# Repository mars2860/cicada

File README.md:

### About

The Cicada Project is the flight controller based on ESP8266 Wifi module. You can make it yourself to come in the world of drone developers. Cicada doesn't have a hardware pult with sticks. To control a drone there is desktop application developed on Java and mobile application for Android v7 and higher. You can connect a gamepad to your smartphone or desktop to control a drone. The flight controller can work in WiFi normal mode as WiFi station or WiFi Access Point. Also It can work in WiFi Broadcast mode (WiFi monitor mode). To work in broadcast mode you have to connect the special wifi broadcast serial modem to your smartphone or desktop. The serial modem is easy. You can do it yourself easy. Just ESP-07 module + UART-USB bridge. Flash in ESP-07 the modem firmware which is placed in the folder /firmware/WifiBroadcastModemFw.

### Features

|     |     |     |     |
| --- | --- | --- | --- |
|     | **Min** | **Typ** | **Max** |
| **1\. Supply voltage** | 3,4V |     | 5V  |
| **2\. Update frequency** |     | 100 Hz |     |
| **3\. Control from notebook or smartphone through WiFi net.** |     | 2.4 GHz |     |
| **4\. Instant telemetry through WiFi net.** Charts of all parameters. BlackBox is stored on host. Telemetry packets is sent every 10ms. |     |     |     |
| **5\. Control devices:**<br><br>* Gamepad (supported by desktop and mobile applications)<br>* Keyboard (supported by desktop application only)<br>* Virtual keyboard (supported by desktop application only)<br>* Virtual gamepad (supported by mobile application only) |     |     |     |
| **6\. Control range** |     |     | 100 meters |
| **7\. Stabilization modes:**<br><br>* Stabilization of body angular rates<br>* Stabilization of yaw,pitch,roll angles<br>* Stabilization of vertical velocity (only if barometer or lidar are available in the system)<br>* Stabilization of horizontal velocity (only if optical flow sensor or GPS are available in the system) |     |     |     |
| **8\. Supported sensors and devices:**<br><br>* MPU9250 - imu chip<br>* MPU6500 - imu chip<br>* MPU6050 - imu chip<br>* QMC5883L - magnetometer<br>* BMP280 - barometer<br>* VL53L1X - lidar<br>* TFmini Plus (in I2C mode) - lidar<br>* HCSR04 (in I2C mode) - sonar<br>* BN180 and other GPS modules with UBX protocol<br>* Analog 0-3V sensor of battery current<br>* Servo 500-2400us to control camera pitch angle<br>* Camera Runcam Split4 (only supported start/stop video commands) |     |     |     |
| **9\. Electronic speed controllers:**<br><br>* DSHOT-300 to control BLDC motors<br>* All listed below PWM-modesе to direct control coreless dc motors<br>* PWM 2.5 kHz, resolution 2000<br>* PWM 5 kHz, resolution 1000<br>* PWM 10 kHz, resolution 500<br>* PWM 20 kHz, resolution 250<br>* PWM 40 kHz, resolution 125<br>* PWM 50 kHz, resolution 100 |     |     |     |
| **10\. Dimensions**<br><br>* cicada-main-v4<br>* cicada-micro-v2 |     | 58,67mm х 41,65mm  <br>26,67mm x 30,98mm |     |
| **11\. Installation dimensions**<br><br>* cicada-main-v4<br>* cicada-micro-v2 |     | 48,51mm х 31,49mm  <br>21,84mm x 26,16mm |     |
| **12\. Weight**<br><br>* cicada-main-v4 with cicada-gy91-v3<br>* cicada-micro-v2 |     | 16g  <br>6g |     |
	
### Drones

Examples of drones you can find in drones folder of this project.

### Firmware

The firmware is based on PDL. Portable Drone Logic (PDL) is the lightweight pure C library implements a common drone logic. The goal of PDL is to be easy to use and easy to port to your hardware platform. PDL supports only quadcopters at this time.

It provides for you
- data model
- application template
- task scheduler
- chain of PIDs
- parser for binary digital commands

PDL is a part of this project. But you can use it to create firmware for your own hardware platform. Documentation is available in /firmware/CicadaFw/libraries/pdl

To build firmware you need
- Install Sloeber IDE https://github.com/Sloeber/arduino-eclipse-plugin/releases/
- Run Sloeber IDE. Go to Arduino->Preferences->Platforms and Boards. Download latest version of ESP8266 platform
- Install I2C driver https://github.com/enjoyneering/ESP8266-I2C-Driver
- Create ssid_config.h file with your wifi-net settings. For example

Firmware supports update by the air. It is based on ESP8266HTTPUpdateServer.

### Chain of PIDs

### Design tools

- Sloeber IDE
- FreeCAD
- KiCAD

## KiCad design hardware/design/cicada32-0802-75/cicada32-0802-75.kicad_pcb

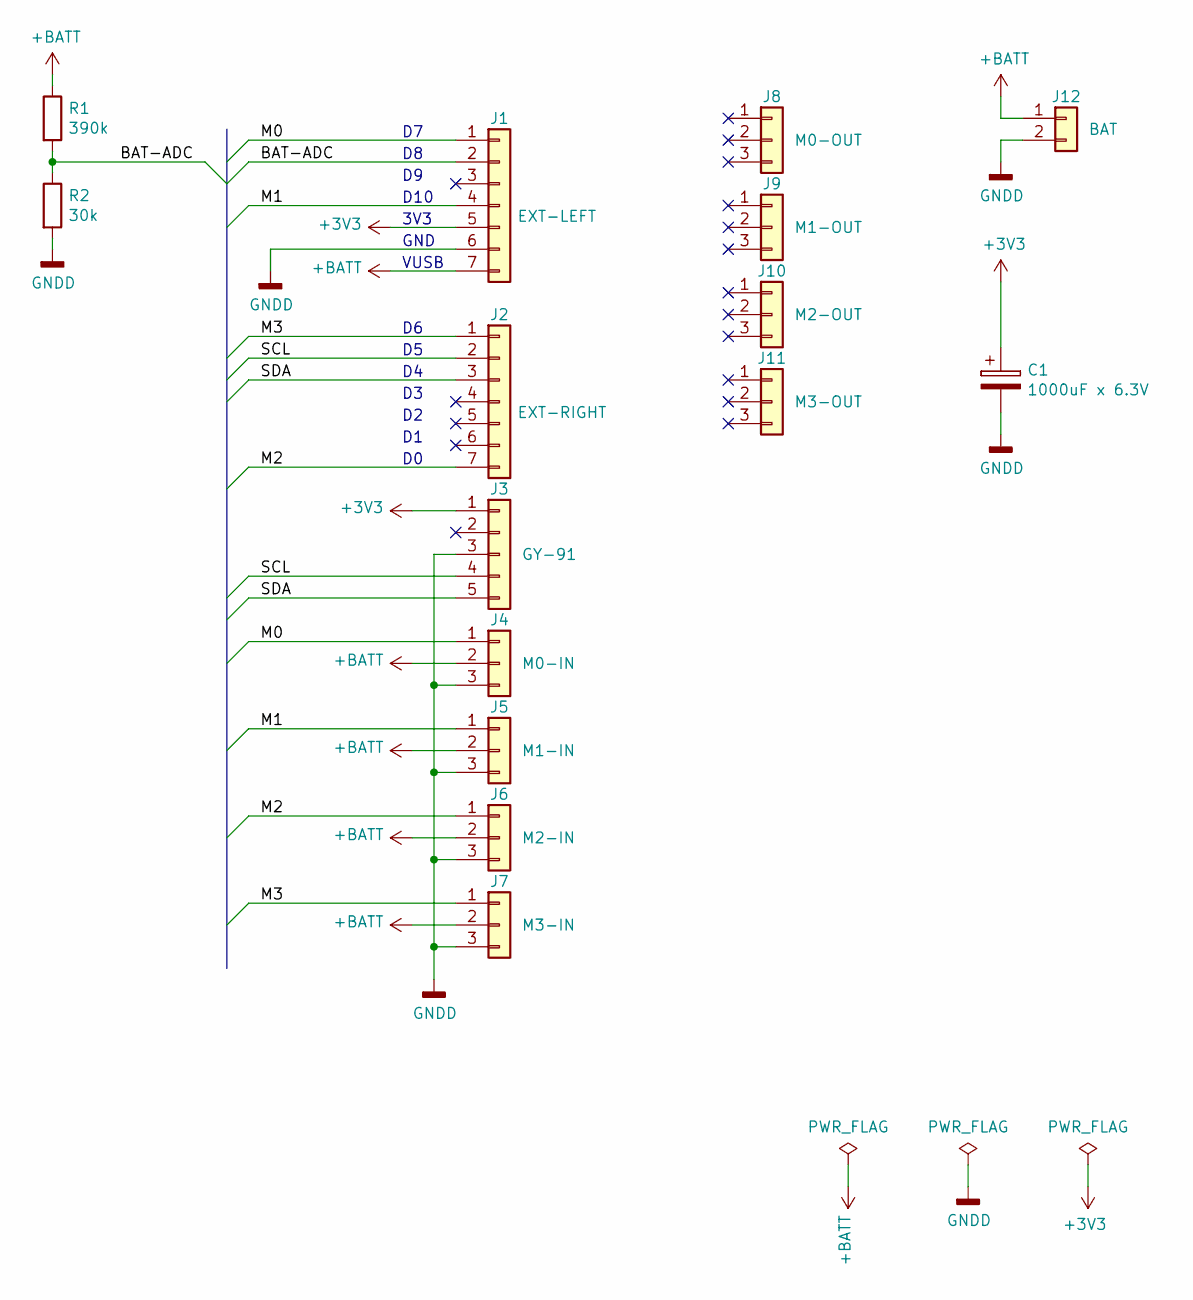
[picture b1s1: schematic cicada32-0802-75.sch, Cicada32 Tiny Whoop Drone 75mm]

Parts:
C1: 1000uF x 6.3V; CP_Radial_D8.0mm_P3.50mm
J1: EXT-LEFT; PinSocket_1x07_P2.54mm_Vertical
J2: EXT-RIGHT; PinSocket_1x07_P2.54mm_Vertical
J3: GY-91; PinHeader_1x05_P2.54mm_Vertical
J4: M0-IN; PinHeader_1x03_P2.54mm_Vertical
J5: M1-IN; PinHeader_1x03_P2.54mm_Vertical
J6: M2-IN; PinHeader_1x03_P2.54mm_Vertical
J7: M3-IN; PinHeader_1x03_P2.54mm_Vertical
J8: M0-OUT; PinHeader_1x03_P2.54mm_Vertical
J9: M1-OUT; PinHeader_1x03_P2.54mm_Vertical
J10: M2-OUT; PinHeader_1x03_P2.54mm_Vertical
J11: M3-OUT; PinHeader_1x03_P2.54mm_Vertical
J12: BAT; SolderWirePad_1x02_P3.81mm_Drill1.2mm
R1: 390k; R_0805_2012Metric_Pad1.15x1.40mm_HandSolder
R2: 30k; R_0805_2012Metric_Pad1.15x1.40mm_HandSolder

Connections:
+3V3: C1.1, J1.5, J3.1
+BATT: J1.7, J4.2, J5.2, J6.2, J7.2, J12.1, R1.1
/BAT-ADC: J1.2, R1.2, R2.1
/M0: J1.1, J4.1
/M1: J1.4, J5.1
/M2: J2.7, J6.1
/M3: J2.1, J7.1
/SCL: J2.2, J3.4
/SDA: J2.3, J3.5
GNDD: C1.2, J1.6, J3.3, J4.3, J5.3, J6.3, J7.3, J12.2, R2.2

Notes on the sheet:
D10
3V3
GND
VUSB

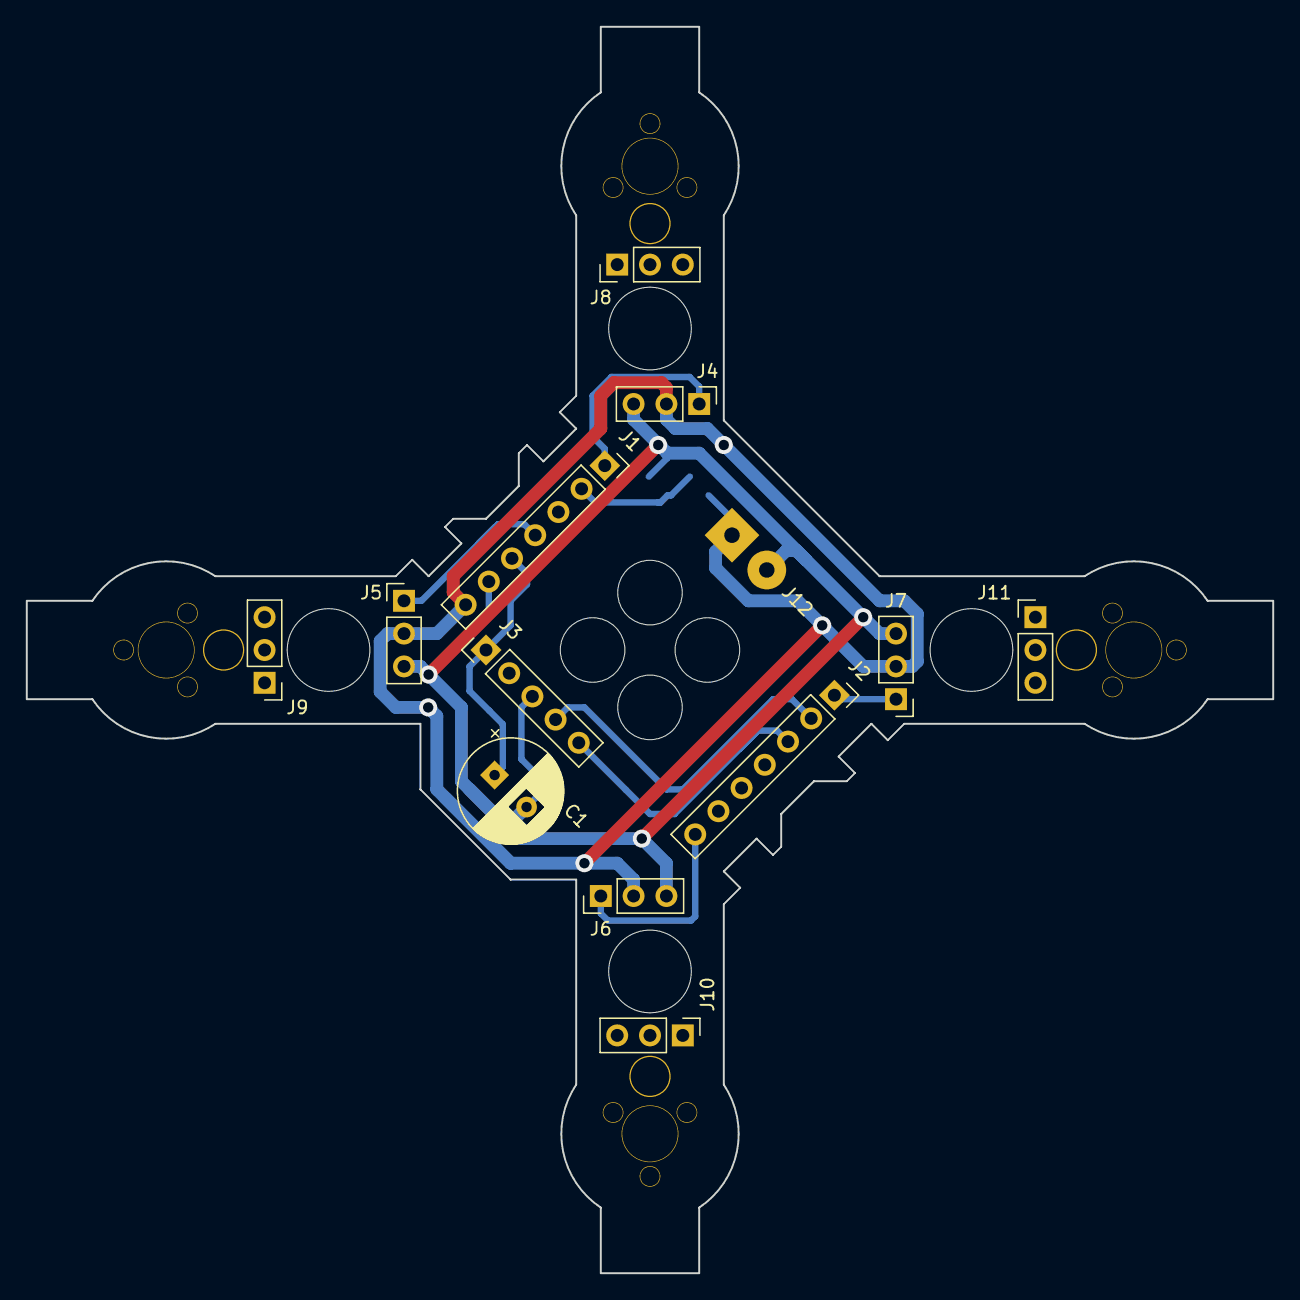
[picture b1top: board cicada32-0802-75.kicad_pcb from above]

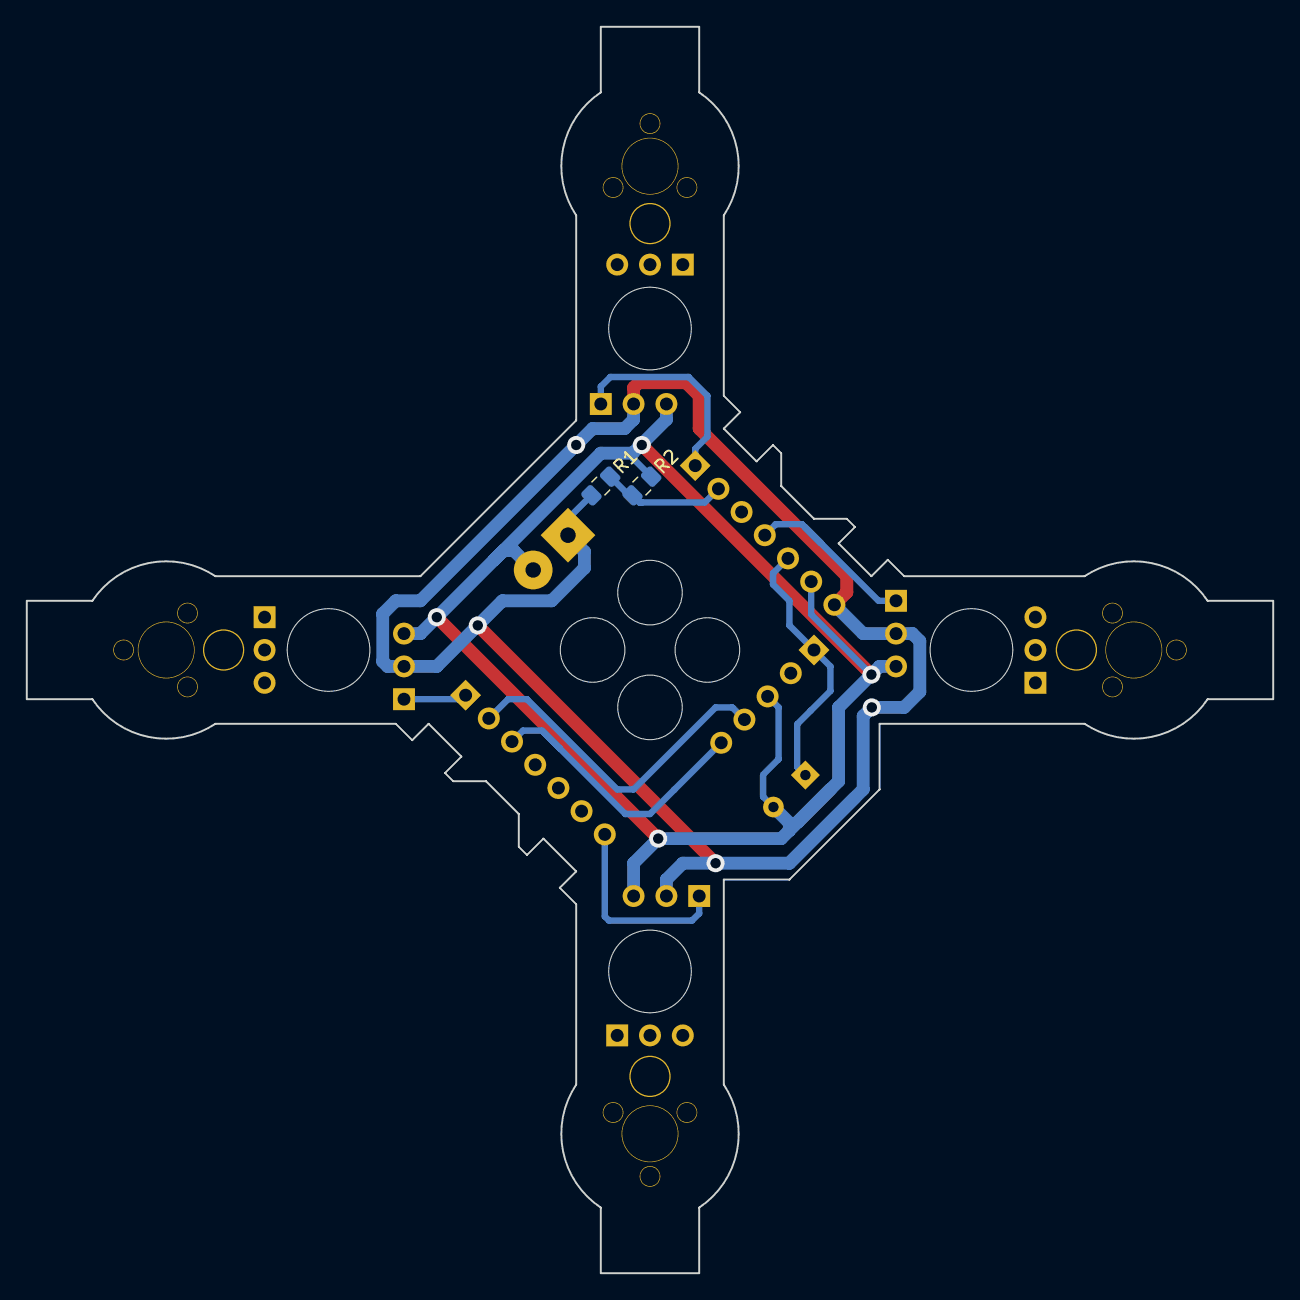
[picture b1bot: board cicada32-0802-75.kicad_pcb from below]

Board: 2 copper layers, 96.5 x 96.5 mm, 15 parts (2 on the bottom side), 10 nets.

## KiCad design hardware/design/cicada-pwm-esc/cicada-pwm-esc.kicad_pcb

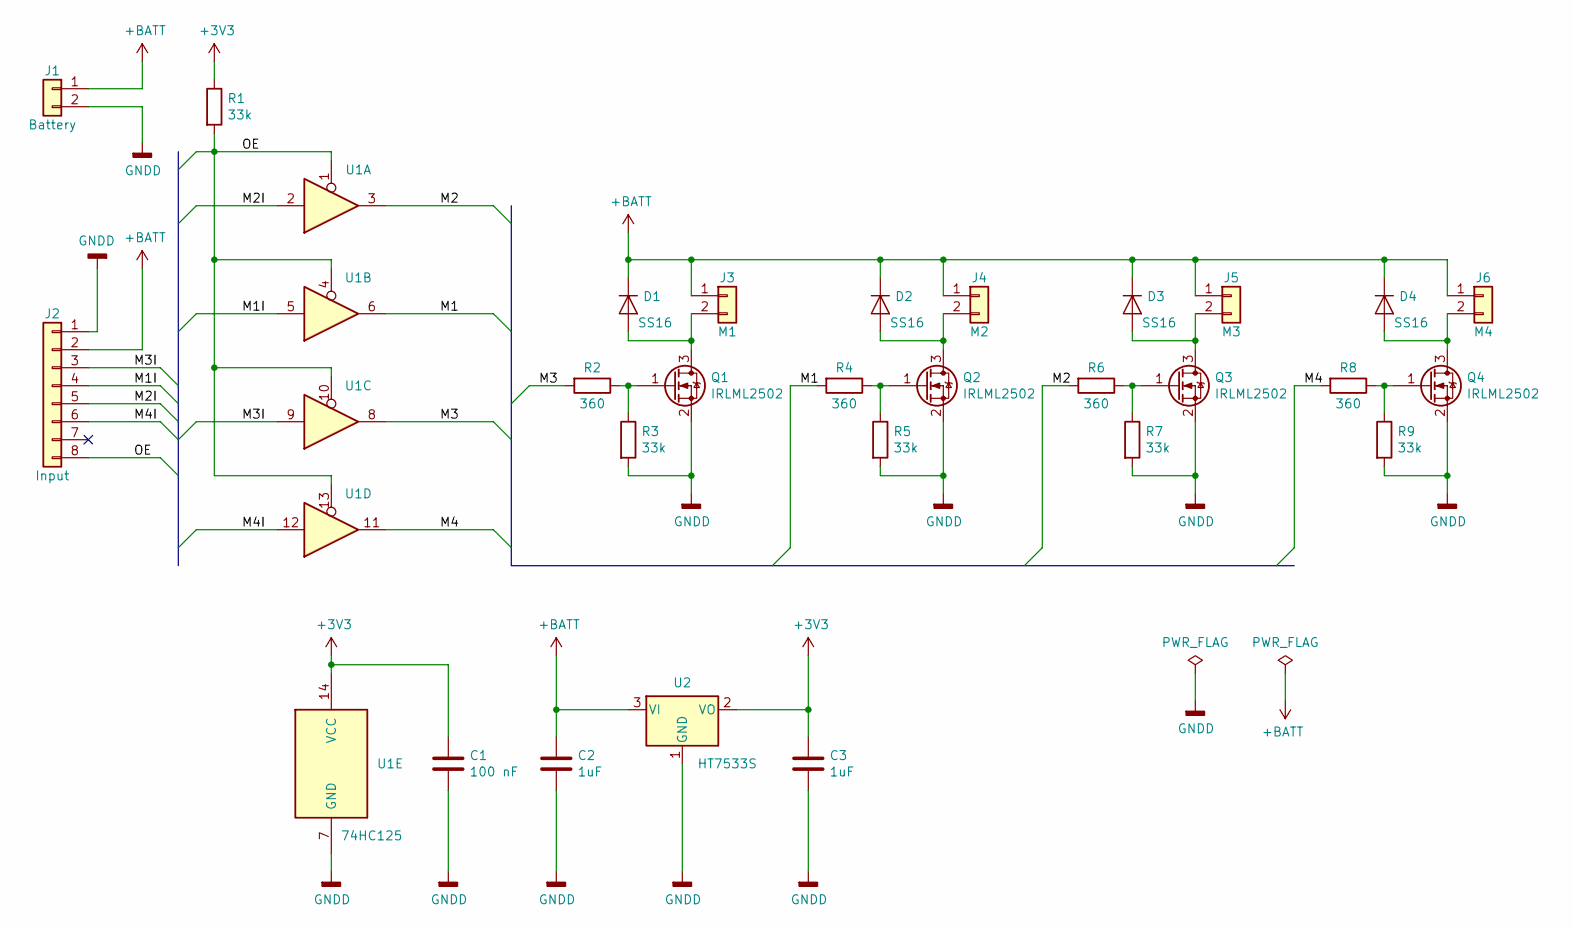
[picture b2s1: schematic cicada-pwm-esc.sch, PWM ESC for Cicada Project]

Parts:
C1: 100 nF; C_0805_2012Metric
C2, C3: 1uF; C_0805_2012Metric
D1, D2, D3, D4: SS16; D_SMA
J1: Battery; SolderWirePad_1x02_P5.08mm_Drill1.5mm
J2: Input; Molex_PicoBlade_53047-1610_1x08_P1.25mm_Vertical
J3: M1; Molex_PicoBlade_53047-0410_1x02_P1.25mm_Vertical
J4: M2; Molex_PicoBlade_53047-0410_1x02_P1.25mm_Vertical
J5: M3; Molex_PicoBlade_53047-0410_1x02_P1.25mm_Vertical
J6: M4; Molex_PicoBlade_53047-0410_1x02_P1.25mm_Vertical
Q1, Q2, Q3, Q4: IRLML2502; SOT-23
R1, R3, R5, R7, R9: 33k; R_0805_2012Metric
R2, R4, R6, R8: 360; R_0805_2012Metric
U1: 74HC125; SOIC-14_3.9x8.7mm_P1.27mm
U2: HT7533S; SOT-23

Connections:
+3V3: C1.1, C3.1, R1.1, U1.14 (VCC), U2.2 (VO)
+BATT: C2.1, D1.1 (K), D2.1 (K), D3.1 (K), D4.1 (K), J1.1, J2.2, J3.1, J4.1, J5.1, J6.1, U2.3 (VI)
/M1: R4.2, U1.6
/M1I: J2.4, U1.5
/M2: R6.2, U1.3
/M2I: J2.5, U1.2
/M3: R2.2, U1.8
/M3I: J2.3, U1.9
/M4: R8.2, U1.11
/M4I: J2.6, U1.12
/OE: J2.8, R1.2, U1.1, U1.4, U1.10, U1.13
GNDD: C1.2, C2.2, C3.2, J1.2, J2.1, Q1.2 (S), Q2.2 (S), Q3.2 (S), Q4.2 (S), R3.2, R5.2, R7.2, R9.2, U1.7 (GND), U2.1 (GND)
unnamed: D1.2 (A), J3.2, Q1.3 (D)
unnamed: D2.2 (A), J4.2, Q2.3 (D)
unnamed: D3.2 (A), J5.2, Q3.3 (D)
unnamed: D4.2 (A), J6.2, Q4.3 (D)
unnamed: Q1.1 (G), R2.1, R3.1
unnamed: Q2.1 (G), R4.1, R5.1
unnamed: Q3.1 (G), R6.1, R7.1
unnamed: Q4.1 (G), R8.1, R9.1

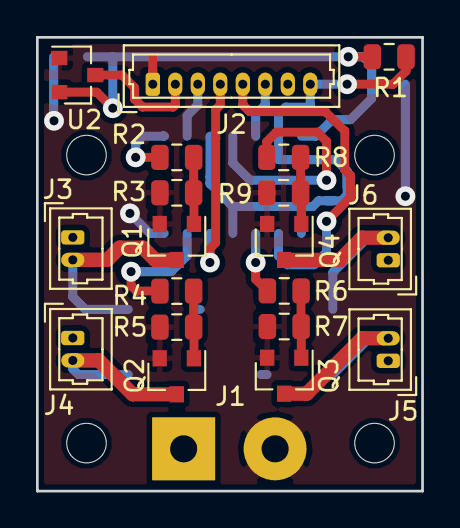
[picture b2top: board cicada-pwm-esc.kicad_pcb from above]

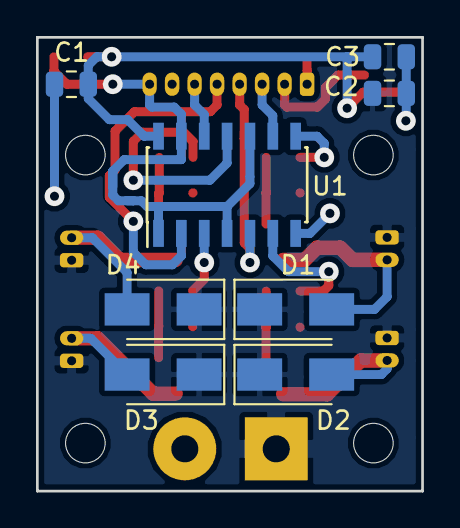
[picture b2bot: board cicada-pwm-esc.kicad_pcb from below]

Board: 2 copper layers, 21.4 x 25.2 mm, 28 parts (8 on the bottom side), 20 nets.

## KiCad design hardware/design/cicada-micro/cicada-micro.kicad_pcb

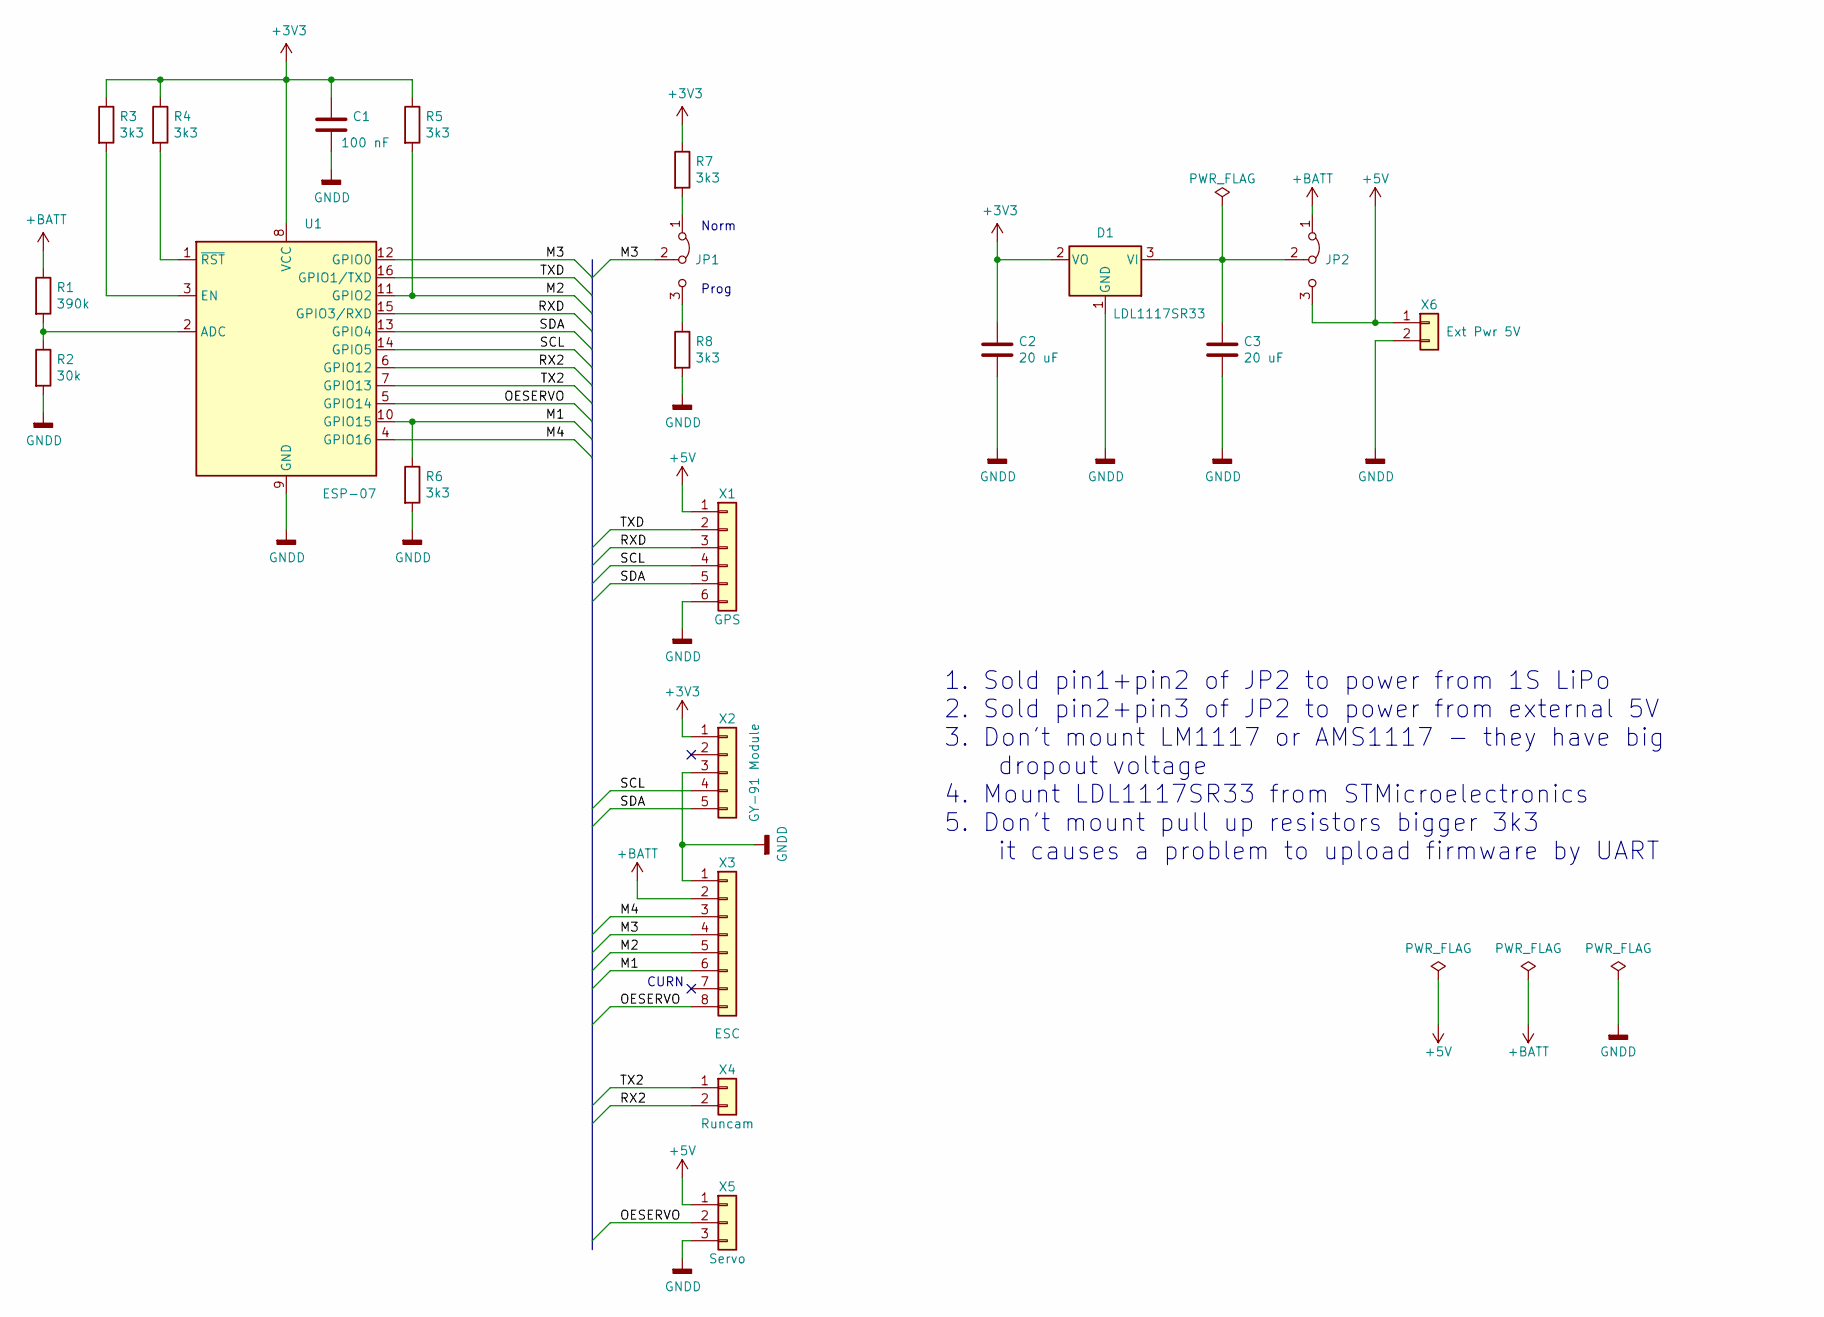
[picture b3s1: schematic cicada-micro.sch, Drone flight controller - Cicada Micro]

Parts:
C1: 100 nF; C_0805_2012Metric
C2, C3: 20 uF; C_1206_3216Metric
D1: LDL1117SR33; SOT-223-3_TabPin2
JP1, JP2: Jumper_3_Bridged12; SolderJumper-3_P1.3mm_Open_Pad1.0x1.5mm
R1: 390k; R_0805_2012Metric
R2: 30k; R_0805_2012Metric
R3, R4, R5, R6, R7, R8: 3k3; R_0805_2012Metric
U1: ESP-07; ESP-07-ThroughMount
X1: GPS; Molex_PicoBlade_53047-1210_1x06_P1.25mm_Vertical
X2: GY-91 Module; PinHeader_1x05_P2.54mm_Vertical
X3: ESC; Molex_PicoBlade_53047-1610_1x08_P1.25mm_Vertical
X4: Runcam; Molex_PicoBlade_53047-0410_1x02_P1.25mm_Vertical
X5: Servo; Molex_PicoBlade_53047-0610_1x03_P1.25mm_Vertical
X6: Ext Pwr 5V; Molex_PicoBlade_53047-0410_1x02_P1.25mm_Vertical

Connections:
+3V3: C1.1, C2.1, D1.2 (VO), R3.1, R4.1, R5.1, R7.1, U1.8 (VCC), X2.1
+5V: JP2.3 (B), X1.1, X5.1, X6.1; also elsewhere on the board
+BATT: JP2.1 (A), R1.1, X3.2; also elsewhere on the board
/M1: R6.1, U1.10 (GPIO15), X3.6
/M2: R5.2, U1.11 (GPIO2), X3.5
/M3: JP1.2 (C), U1.12 (GPIO0), X3.4
/M4: U1.4 (GPIO16), X3.3
/OESERVO: U1.5 (GPIO14), X3.8, X5.2
/RX2: U1.6 (GPIO12), X4.2
/RXD: U1.15 (GPIO3/RXD), X1.3
/SCL: U1.14 (GPIO5), X1.4, X2.4
/SDA: U1.13 (GPIO4), X1.5, X2.5
/TX2: U1.7 (GPIO13), X4.1
/TXD: U1.16 (GPIO1/TXD), X1.2
GNDD: C1.2, C2.2, C3.2, D1.1 (GND), R2.2, R6.2, R8.2, U1.9 (GND), X1.6, X2.3, X3.1, X5.3, X6.2
unnamed 15: C3.1, D1.3 (VI), JP2.2 (C); also elsewhere on the board
unnamed: JP1.1 (A), R7.2
unnamed: JP1.3 (B), R8.1
unnamed: R1.2, R2.1, U1.2 (ADC)
unnamed: R3.2, U1.3 (EN)
unnamed: R4.2, U1.1 (~RST)

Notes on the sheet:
Norm
Prog
CURN
1. Sold pin1+pin2 of JP2 to power from 1S LiPo 2. Sold pin2+pin3 of JP2 to power from external 5V 3. Don't mount LM1117 or AMS1117 - they have big dropout voltage 4. Mount LDL1117SR33 from STMicroelectronics 5. Don't mount pull up resistors bigger 3k3 it causes a problem to upload firmware by UART

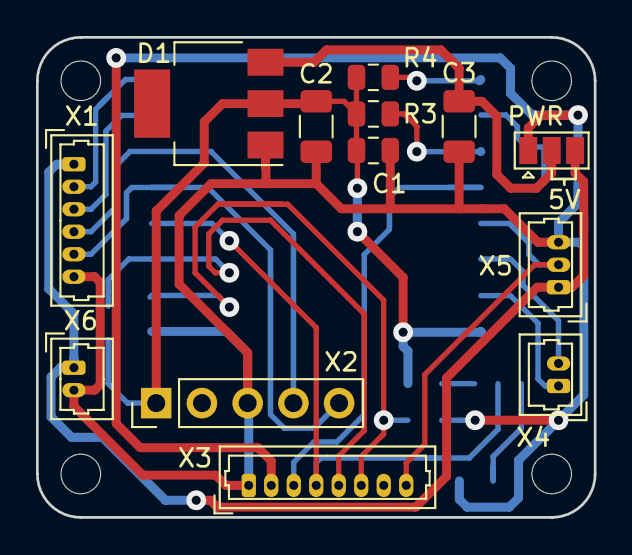
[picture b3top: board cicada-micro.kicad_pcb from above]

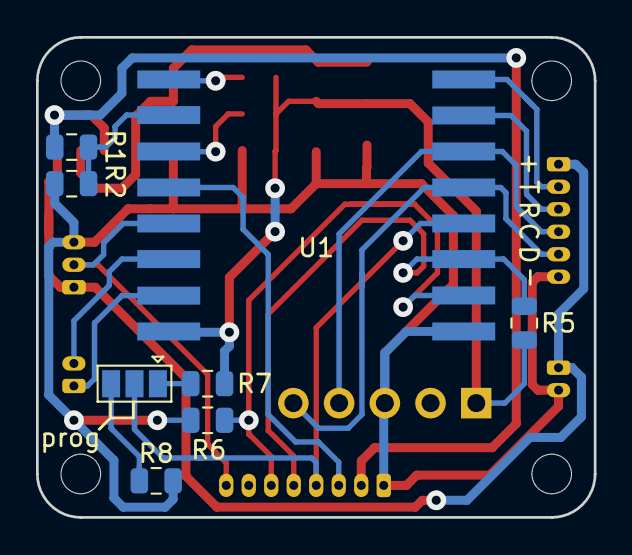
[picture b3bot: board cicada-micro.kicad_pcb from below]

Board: 2 copper layers, 31.0 x 26.7 mm, 21 parts (8 on the bottom side), 21 nets.

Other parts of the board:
PWR: Jumper_3_Bridged12; SolderJumper-3_P1.3mm_Open_Pad1.0x1.5mm

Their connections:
+5V: PWR.3; also elsewhere on the board
+BATT: PWR.1; also elsewhere on the board
unnamed 15: PWR.2; also elsewhere on the board

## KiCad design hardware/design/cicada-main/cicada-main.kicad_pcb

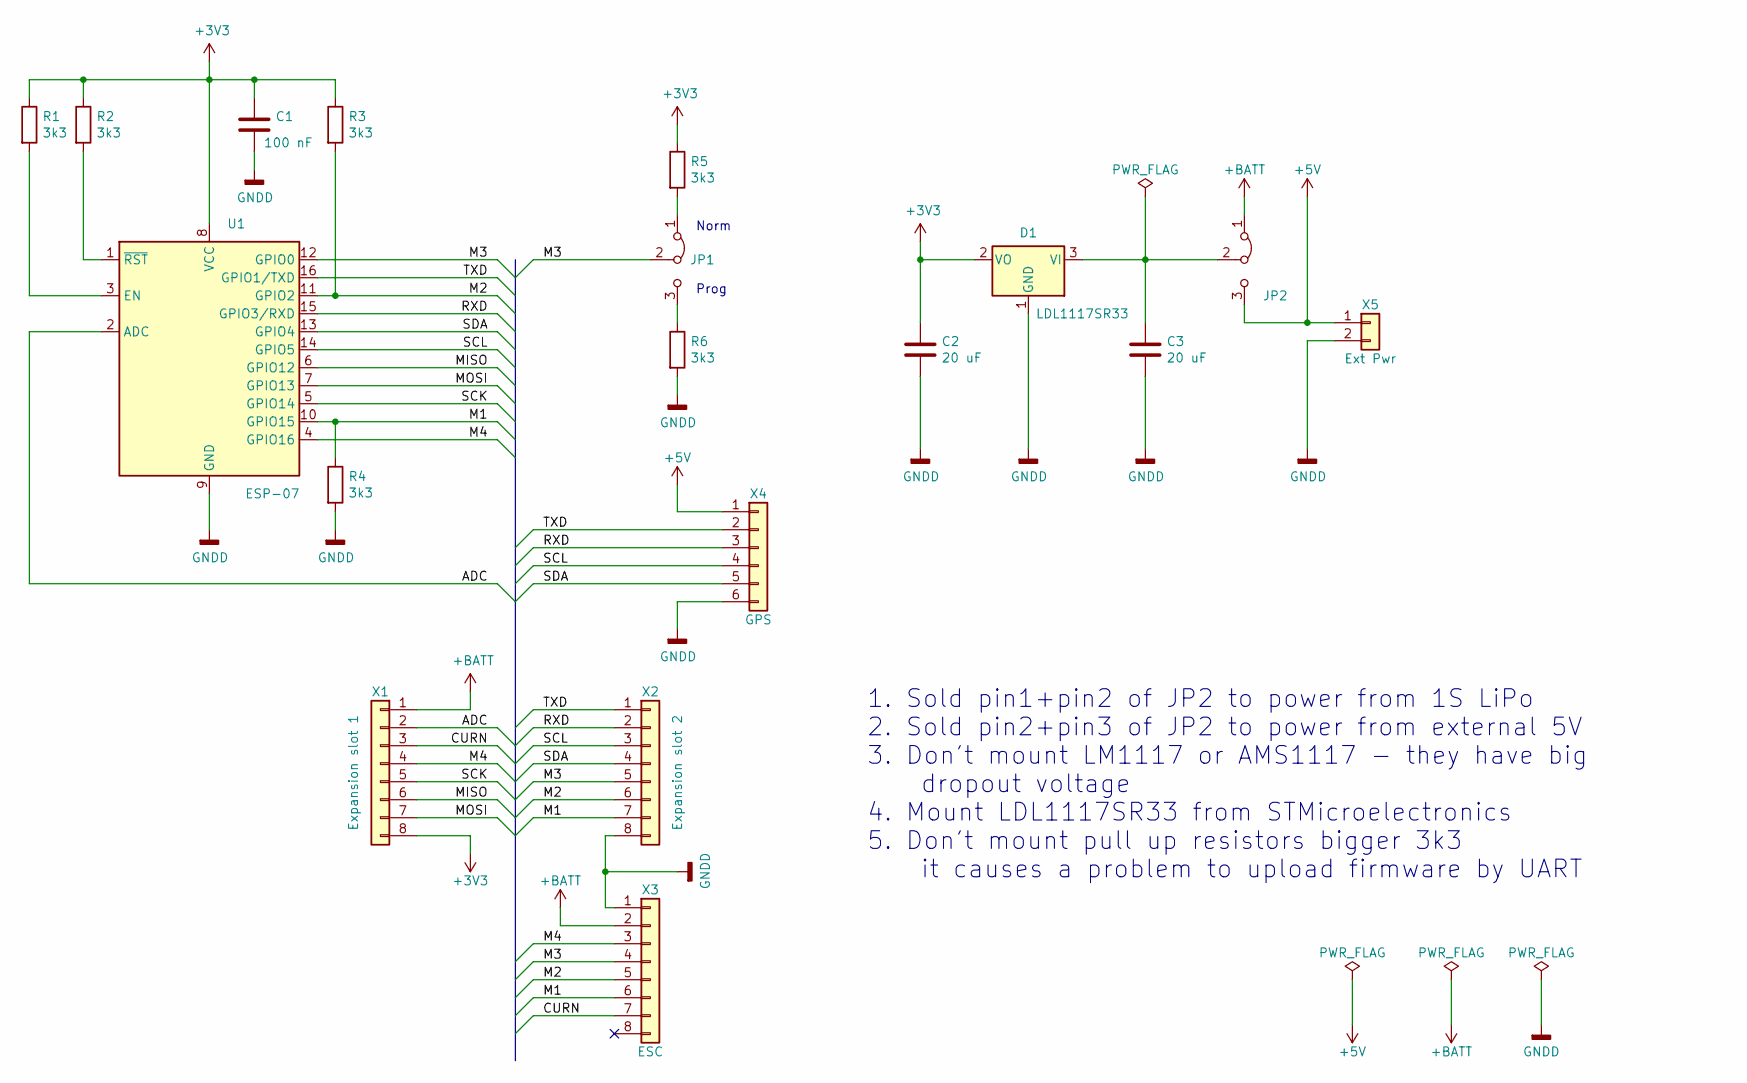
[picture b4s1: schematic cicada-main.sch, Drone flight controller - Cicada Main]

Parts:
C1: 100 nF; C_0805_2012Metric
C2, C3: 20 uF; C_1206_3216Metric
D1: LDL1117SR33; SOT-223-3_TabPin2
JP1, JP2: Jumper_3_Bridged12; SolderJumper-3_P1.3mm_Open_Pad1.0x1.5mm
R1, R2, R3, R4, R5, R6: 3k3; R_0805_2012Metric
U1: ESP-07; ESP-07-ThroughMount
X1: Expansion slot 1; PinHeader_1x08_P2.54mm_Vertical
X2: Expansion slot 2; PinHeader_1x08_P2.54mm_Vertical
X3: ESC; Molex_PicoBlade_53047-1610_1x08_P1.25mm_Vertical
X4: GPS; Molex_PicoBlade_53047-1210_1x06_P1.25mm_Vertical
X5: Ext Pwr; Molex_PicoBlade_53047-0410_1x02_P1.25mm_Vertical

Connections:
+3V3: C1.1, C2.1, D1.2 (VO), R1.1, R2.1, R3.1, R5.1, U1.8 (VCC), X1.8
+5V: JP2.3 (B), X4.1, X5.1
+BATT: JP2.1 (A), X1.1, X3.2
/ADC: U1.2 (ADC), X1.2
/CURN: X1.3, X3.7
/M1: R4.1, U1.10 (GPIO15), X2.7, X3.6
/M2: R3.2, U1.11 (GPIO2), X2.6, X3.5
/M3: JP1.2 (C), U1.12 (GPIO0), X2.5, X3.4
/M4: U1.4 (GPIO16), X1.4, X3.3
/MISO: U1.6 (GPIO12), X1.6
/MOSI: U1.7 (GPIO13), X1.7
/RXD: U1.15 (GPIO3/RXD), X2.2, X4.3
/SCK: U1.5 (GPIO14), X1.5
/SCL: U1.14 (GPIO5), X2.3, X4.4
/SDA: U1.13 (GPIO4), X2.4, X4.5
/TXD: U1.16 (GPIO1/TXD), X2.1, X4.2
GNDD: C1.2, C2.2, C3.2, D1.1 (GND), R4.2, R6.2, U1.9 (GND), X2.8, X3.1, X4.6, X5.2
unnamed: C3.1, D1.3 (VI), JP2.2 (C)
unnamed: JP1.1 (A), R5.2
unnamed: JP1.3 (B), R6.1
unnamed: R1.2, U1.3 (EN)
unnamed: R2.2, U1.1 (~RST)

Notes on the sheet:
Norm
Prog
1. Sold pin1+pin2 of JP2 to power from 1S LiPo 2. Sold pin2+pin3 of JP2 to power from external 5V 3. Don't mount LM1117 or AMS1117 - they have big dropout voltage 4. Mount LDL1117SR33 from STMicroelectronics 5. Don't mount pull up resistors bigger 3k3 it causes a problem to upload firmware by UART

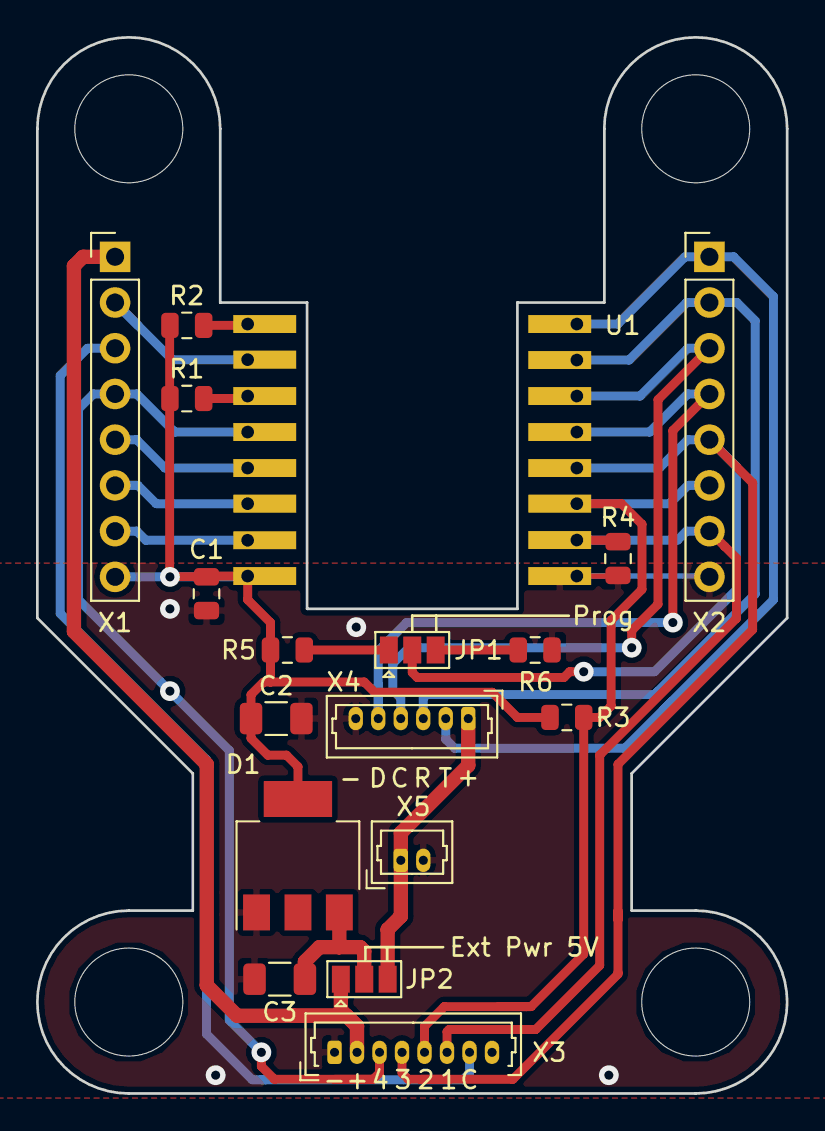
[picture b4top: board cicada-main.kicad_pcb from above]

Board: 2 copper layers, 41.7 x 58.7 mm, 18 parts (0 on the bottom side), 22 nets.

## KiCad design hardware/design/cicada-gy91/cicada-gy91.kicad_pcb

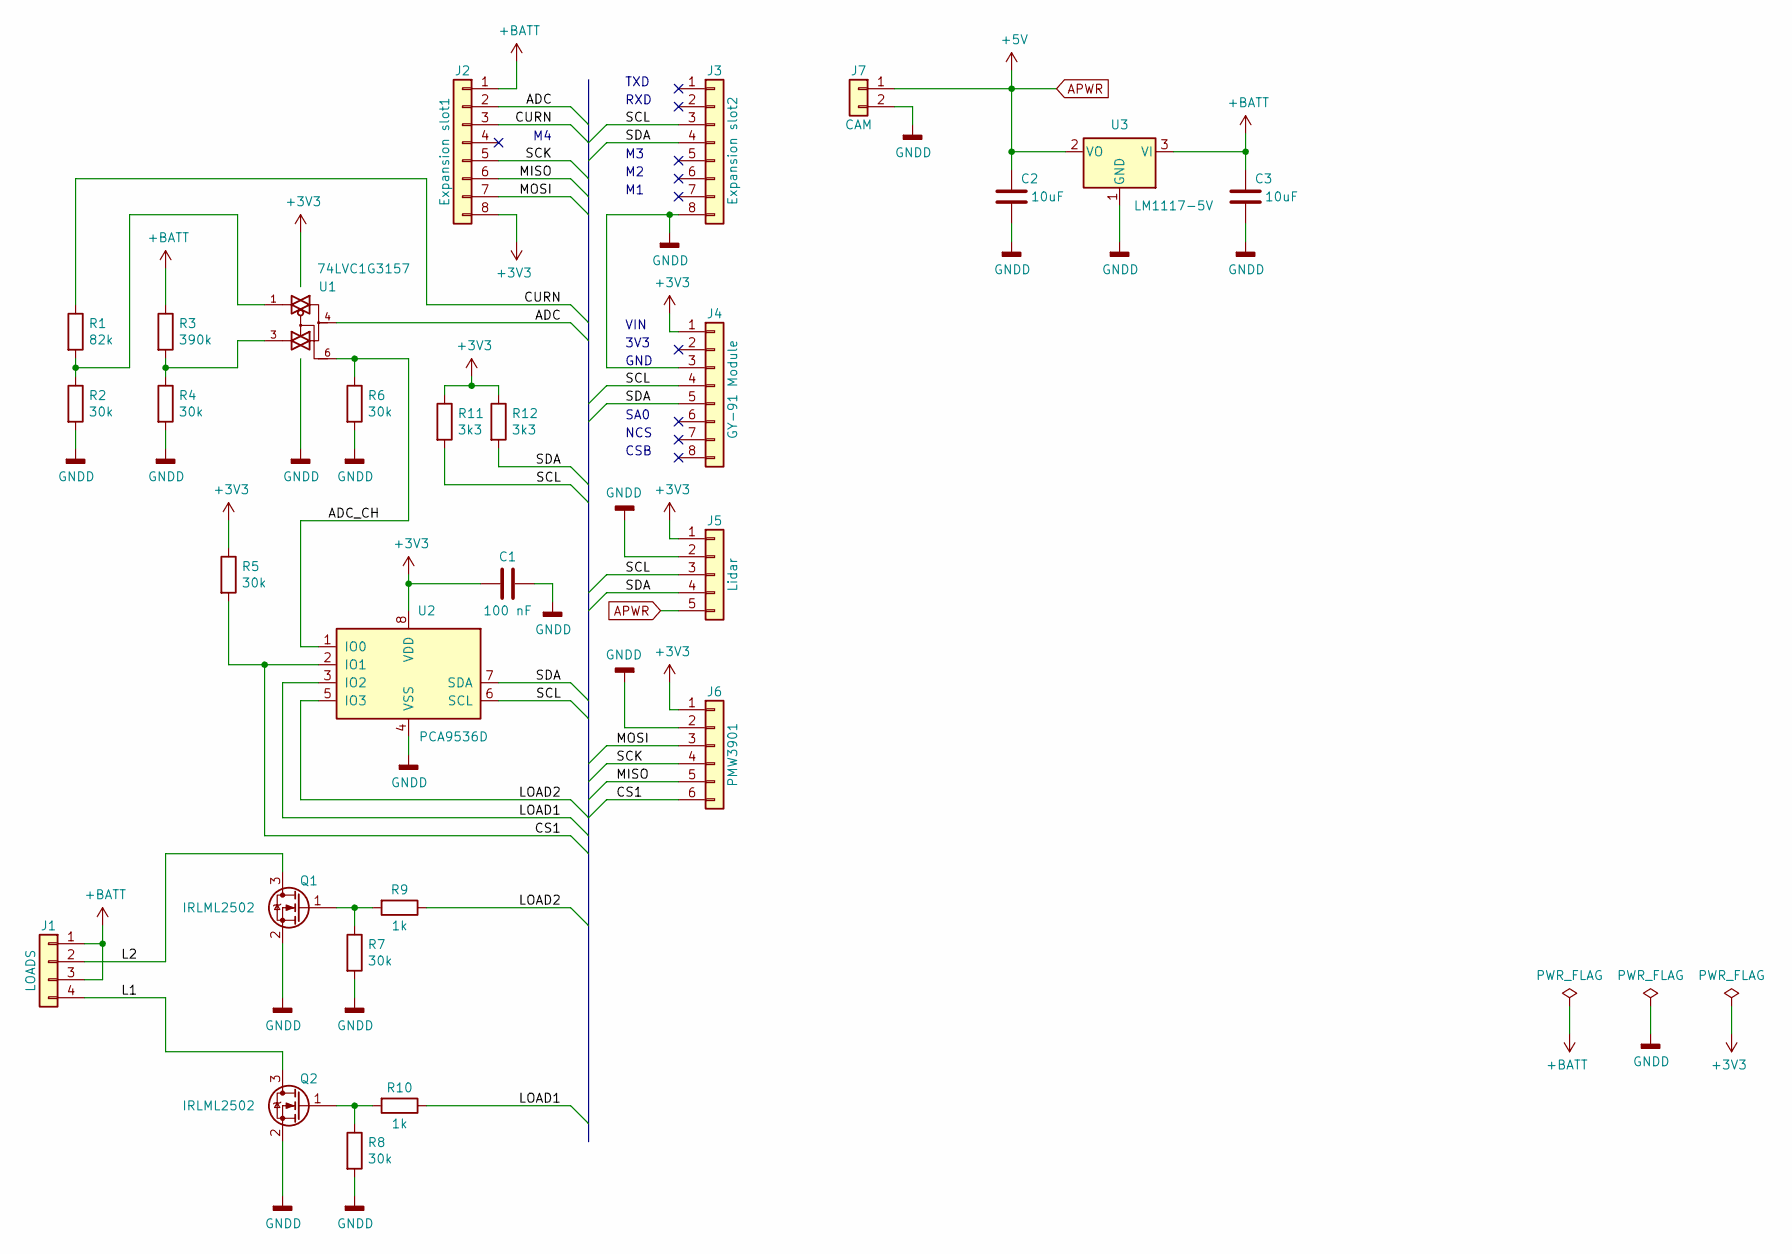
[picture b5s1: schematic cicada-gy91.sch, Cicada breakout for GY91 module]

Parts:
C1: 100 nF; C_0805_2012Metric
C2, C3: 10uF; C_0805_2012Metric
J1: LOADS; Molex_PicoBlade_53048-0810_1x04_P1.25mm_Horizontal
J2: Expansion slot1; PinSocket_1x08_P2.54mm_Vertical
J3: Expansion slot2; PinSocket_1x08_P2.54mm_Vertical
J4: GY-91 Module; PinHeader_1x08_P2.54mm_Vertical
J5: Lidar; Molex_PicoBlade_53048-1010_1x05_P1.25mm_Horizontal
J6: PMW3901; Molex_PicoBlade_53048-1210_1x06_P1.25mm_Horizontal
J7: CAM; Molex_PicoBlade_53048-0410_1x02_P1.25mm_Horizontal
Q1, Q2: IRLML2502; SOT-23
R1: 82k; R_0805_2012Metric
R2, R4, R5, R6, R7, R8: 30k; R_0805_2012Metric
R3: 390k; R_0805_2012Metric
R9, R10: 1k; R_0805_2012Metric
R11, R12: 3k3; R_0805_2012Metric
U1: 74LVC1G3157; SOT-363_SC-70-6
U2: PCA9536D; SOIC-8_3.9x4.9mm_P1.27mm
U3: LM1117-5V; SOT-223

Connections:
+3V3: C1.2, J2.8, J4.1, J5.1, J6.1, R5.1, R11.1, R12.1, U1.5 (VCC), U2.8 (VDD)
+BATT: C3.2, J1.1, J1.3, J2.1, R3.1, U3.3 (VI)
/ADC: J2.2, U1.4
/ADC_CH: R6.1, U1.6, U2.1 (IO0)
/CS1: J6.6, R5.2, U2.2 (IO1)
/CURN: J2.3, R1.1
/L1: J1.4, Q2.3 (D)
/L2: J1.2, Q1.3 (D)
/LOAD1: R10.1, U2.3 (IO2)
/LOAD2: R9.1, U2.5 (IO3)
/MISO: J2.6, J6.5
/MOSI: J2.7, J6.3
/SCK: J2.5, J6.4
/SCL: J3.3, J4.4, J5.3, R11.2, U2.6 (SCL)
/SDA: J3.4, J4.5, J5.4, R12.2, U2.7 (SDA)
APWR: C2.2, J5.5, J7.1, U3.2 (VO)
GND: C1.1, C2.1, C3.1, J3.8, J4.3, J5.2, J6.2, J7.2, Q1.2 (S), Q2.2 (S), R2.2, R4.2, R6.2, R7.2, R8.2, U1.2 (GND), U2.4 (VSS), U3.1 (GND)
unnamed: Q1.1 (G), R7.1, R9.2
unnamed: Q2.1 (G), R8.1, R10.2
unnamed: R1.2, R2.1, U1.1
unnamed: R3.2, R4.1, U1.3

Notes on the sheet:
NCS
CSB
3V3
VIN
GND
TXD
RXD
SA0

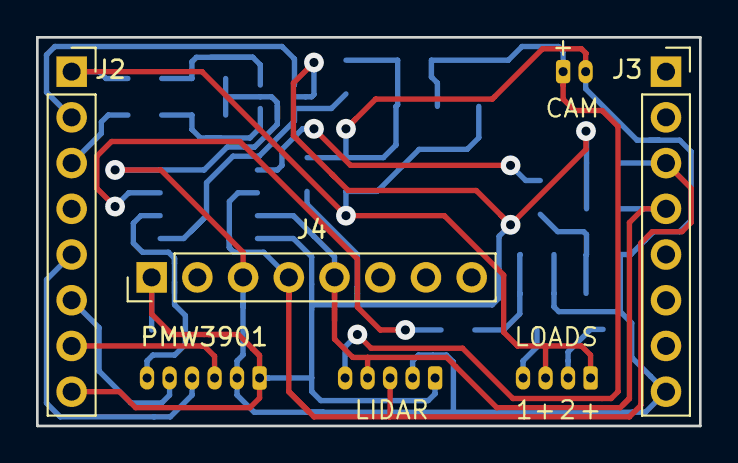
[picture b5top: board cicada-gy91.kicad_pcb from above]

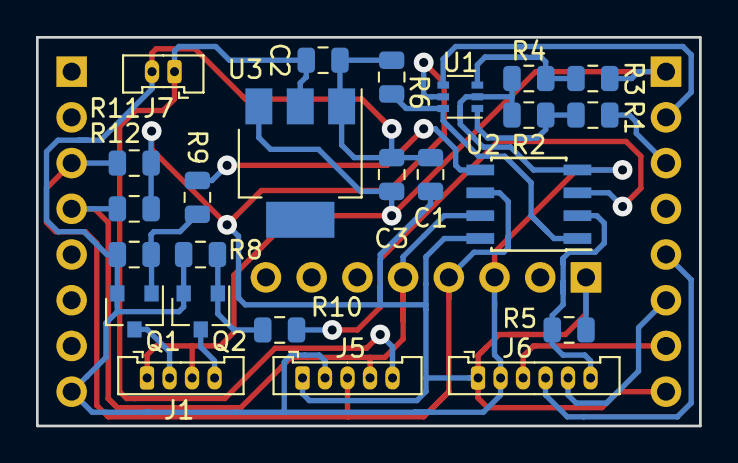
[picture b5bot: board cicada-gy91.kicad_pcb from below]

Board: 2 copper layers, 36.8 x 21.6 mm, 27 parts (24 on the bottom side), 21 nets.
